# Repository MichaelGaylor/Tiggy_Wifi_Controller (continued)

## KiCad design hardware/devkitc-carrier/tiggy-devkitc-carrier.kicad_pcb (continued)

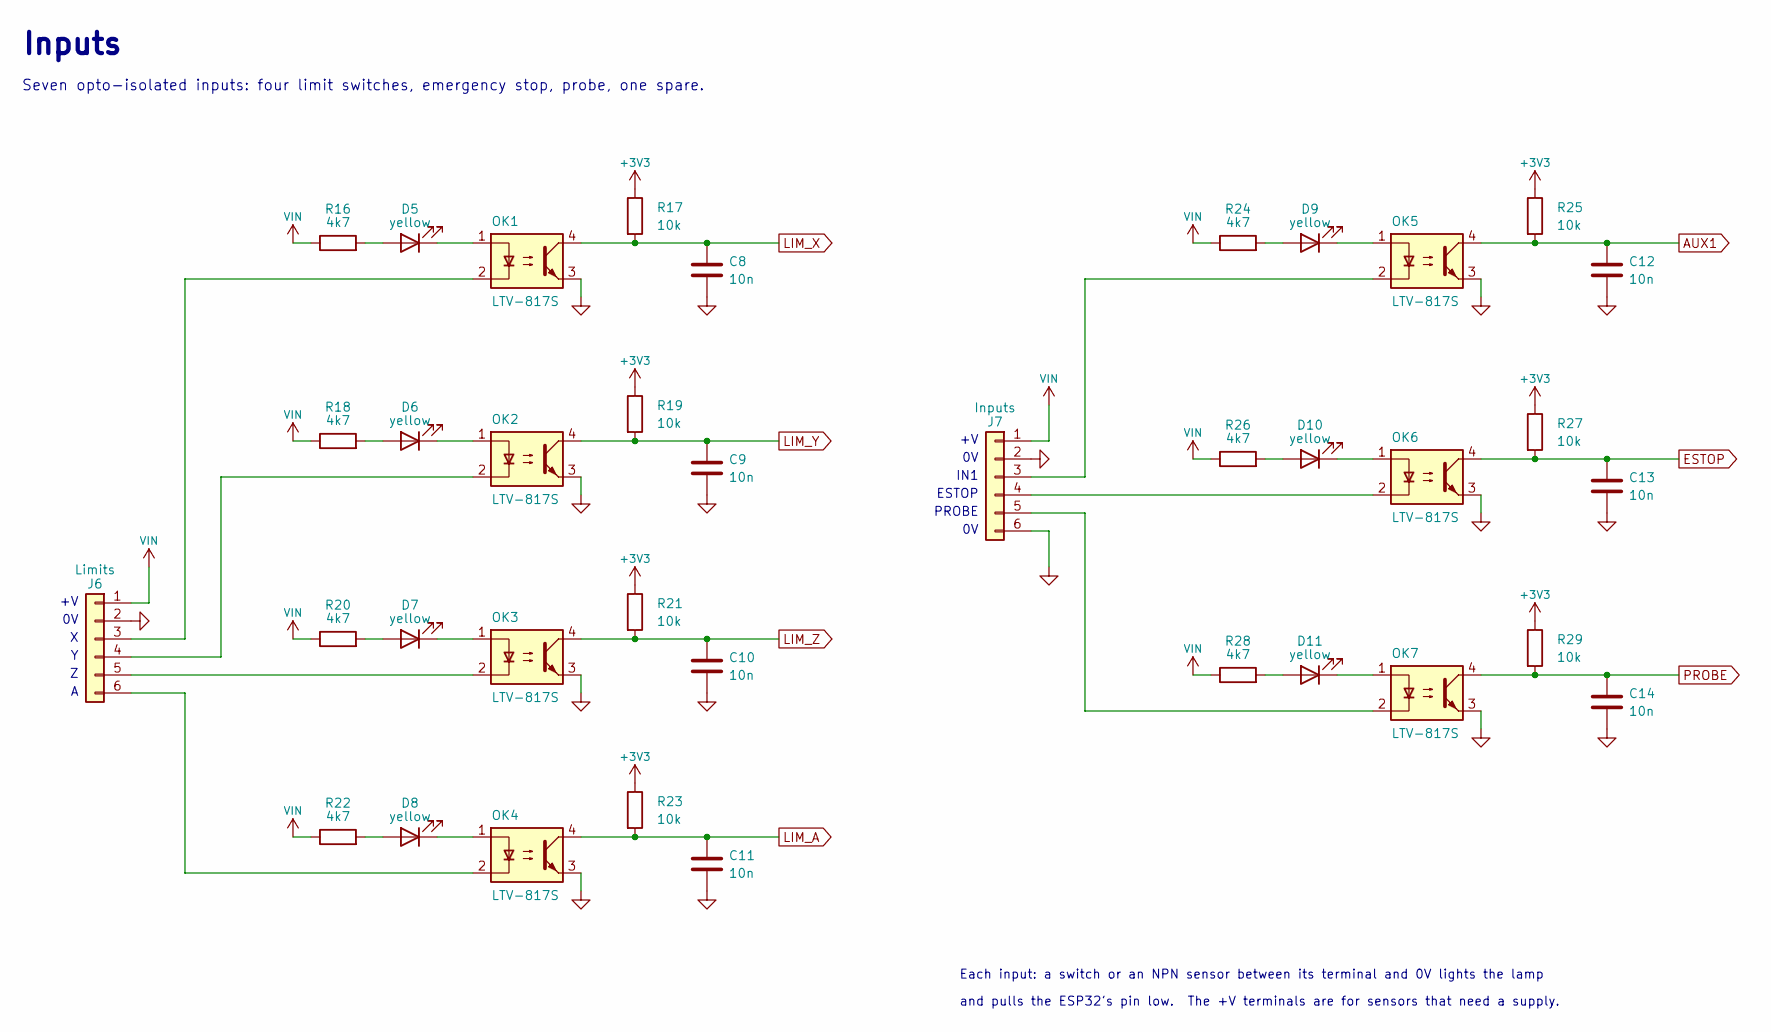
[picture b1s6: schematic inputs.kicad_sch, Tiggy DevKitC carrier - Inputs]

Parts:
C8, C9, C10, C11, C12, C13, C14: 10n; C_0603_1608Metric
D5, D6, D7, D8, D9, D10, D11: yellow; LED_0805_2012Metric
J6: Limits; PhoenixContact_MC_1,5_6-G-3.81_1x06_P3.81mm_Horizontal
J7: Inputs; PhoenixContact_MC_1,5_6-G-3.81_1x06_P3.81mm_Horizontal
OK1, OK2, OK3, OK4, OK5, OK6, OK7: LTV-817S; SMDIP-4_W9.53mm
R16, R18, R20, R22, R24, R26, R28: 4k7; R_1206_3216Metric
R17, R19, R21, R23, R25, R27, R29: 10k; R_0603_1608Metric

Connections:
+3V3: R17.1, R19.1, R21.1, R23.1, R25.1, R27.1, R29.1; also elsewhere on the board
AUX1: C12.1, OK5.4, R25.2; also elsewhere on the board
ESTOP: C13.1, OK6.4, R27.2; also elsewhere on the board
GND: C8.2, C9.2, C10.2, C11.2, C12.2, C13.2, C14.2, J6.2, J7.2, J7.6, OK1.3, OK2.3, OK3.3, OK4.3, OK5.3, OK6.3, OK7.3; also elsewhere on the board
LIM_A: C11.1, OK4.4, R23.2; also elsewhere on the board
LIM_X: C8.1, OK1.4, R17.2; also elsewhere on the board
LIM_Y: C9.1, OK2.4, R19.2; also elsewhere on the board
LIM_Z: C10.1, OK3.4, R21.2; also elsewhere on the board
unnamed: D5.2 (A), R16.2
unnamed: D5.1 (K), OK1.1
unnamed: D6.2 (A), R18.2
unnamed: D6.1 (K), OK2.1
unnamed: D7.2 (A), R20.2
unnamed: D7.1 (K), OK3.1
unnamed: D8.2 (A), R22.2
unnamed: D8.1 (K), OK4.1
unnamed: D9.2 (A), R24.2
unnamed: D9.1 (K), OK5.1
unnamed: D10.2 (A), R26.2
unnamed: D10.1 (K), OK6.1
unnamed: D11.2 (A), R28.2
unnamed: D11.1 (K), OK7.1
unnamed: J6.3, OK1.2
unnamed: J6.4, OK2.2
unnamed: J6.5, OK3.2
unnamed: J6.6, OK4.2
unnamed: J7.3, OK5.2
unnamed: J7.4, OK6.2
unnamed: J7.5, OK7.2
PROBE: C14.1, OK7.4, R29.2; also elsewhere on the board
VIN: J6.1, J7.1, R16.1, R18.1, R20.1, R22.1, R24.1, R26.1, R28.1; also elsewhere on the board

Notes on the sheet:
IN1
ESTOP
PROBE
Each input: a switch or an NPN sensor between its terminal and 0V lights the lamp
and pulls the ESP32's pin low. The +V terminals are for sensors that need a supply.
Inputs
Seven opto-isolated inputs: four limit switches, emergency stop, probe, one spare.

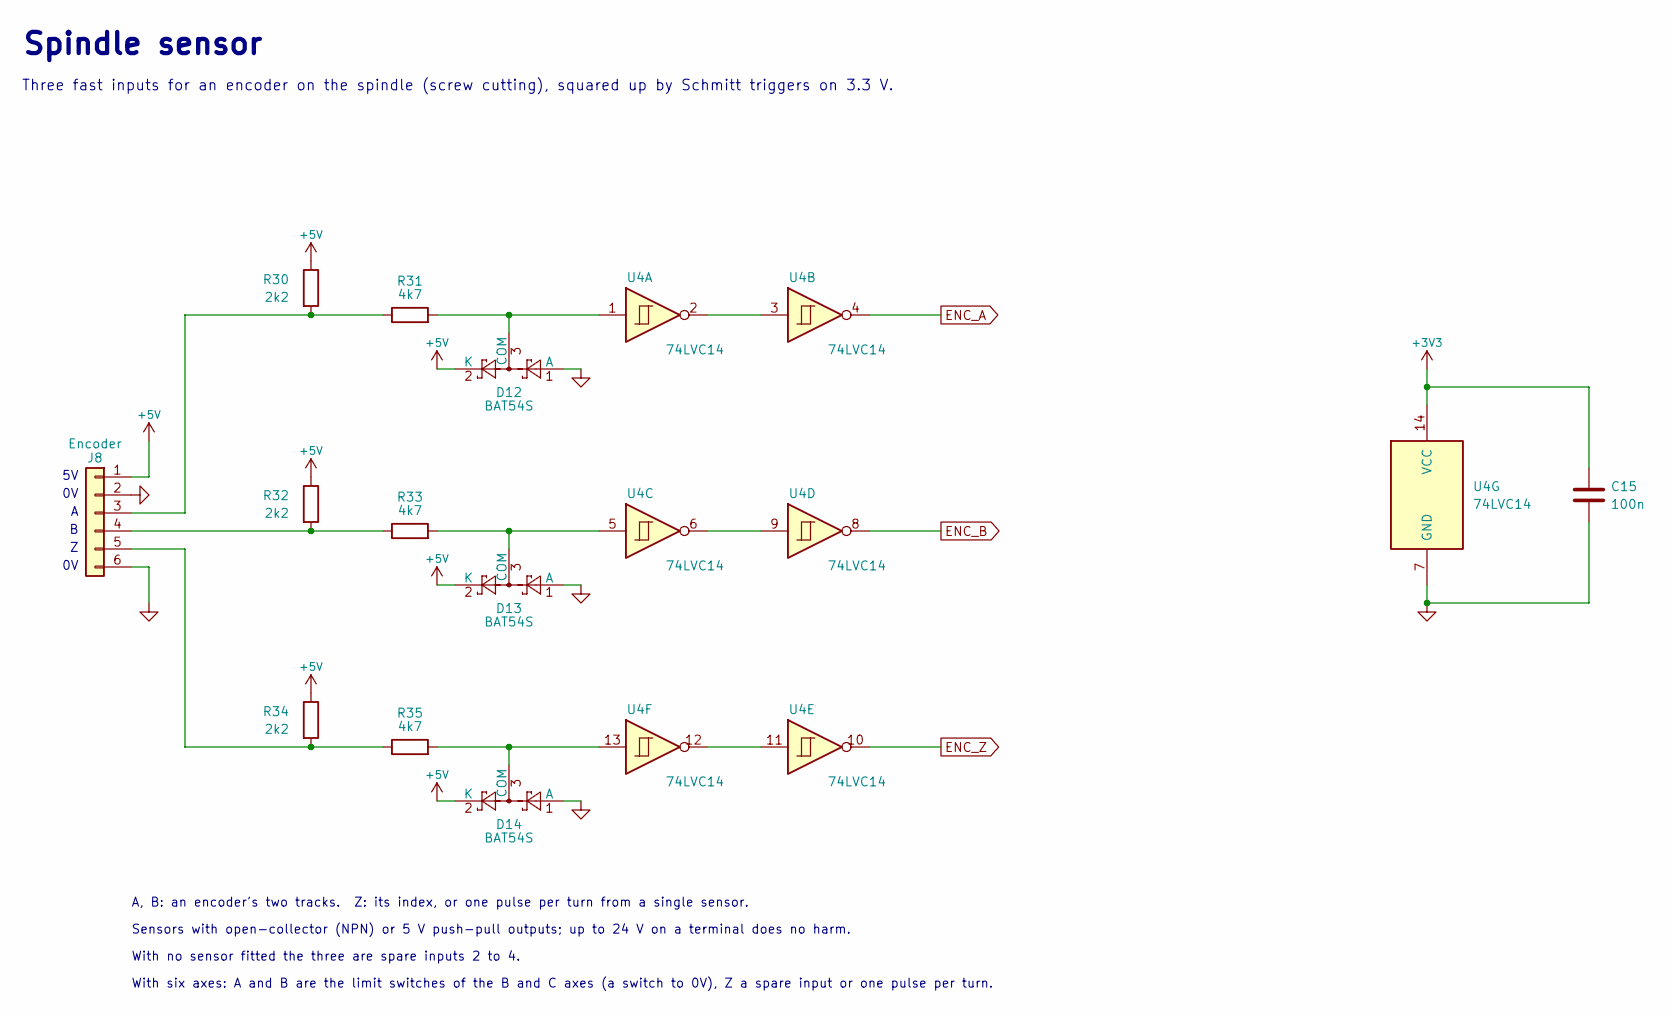
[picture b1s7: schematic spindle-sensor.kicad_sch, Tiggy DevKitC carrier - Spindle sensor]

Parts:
C15: 100n; C_0603_1608Metric
D12, D13, D14: BAT54S; SOT-23
J8: Encoder; PhoenixContact_MC_1,5_6-G-3.81_1x06_P3.81mm_Horizontal
R30, R32, R34: 2k2; R_0603_1608Metric
R31, R33, R35: 4k7; R_0805_2012Metric
U4: 74LVC14; SOIC-14_3.9x8.7mm_P1.27mm

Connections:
+3V3: C15.1, U4.14 (VCC); also elsewhere on the board
+5V: D12.2 (K), D13.2 (K), D14.2 (K), J8.1, R30.1, R32.1, R34.1; also elsewhere on the board
ENC_A: U4.4; also elsewhere on the board
ENC_B: U4.8; also elsewhere on the board
ENC_Z: U4.10; also elsewhere on the board
GND: C15.2, D12.1 (A), D13.1 (A), D14.1 (A), J8.2, J8.6, U4.7 (GND); also elsewhere on the board
unnamed: D12.3 (COM), R31.2, U4.1
unnamed: D13.3 (COM), R33.2, U4.5
unnamed: D14.3 (COM), R35.2, U4.13
unnamed: J8.3, R30.2, R31.1
unnamed: J8.4, R32.2, R33.1
unnamed: J8.5, R34.2, R35.1
unnamed: U4.2, U4.3
unnamed: U4.6, U4.9
unnamed: U4.11, U4.12

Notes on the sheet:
A, B: an encoder's two tracks. Z: its index, or one pulse per turn from a single sensor.
Sensors with open-collector (NPN) or 5 V push-pull outputs; up to 24 V on a terminal does no harm.
With no sensor fitted the three are spare inputs 2 to 4.
With six axes: A and B are the limit switches of the B and C axes (a switch to 0V), Z a spare input or one pulse per turn.
Spindle sensor
Three fast inputs for an encoder on the spindle (screw cutting), squared up by Schmitt triggers on 3.3 V.

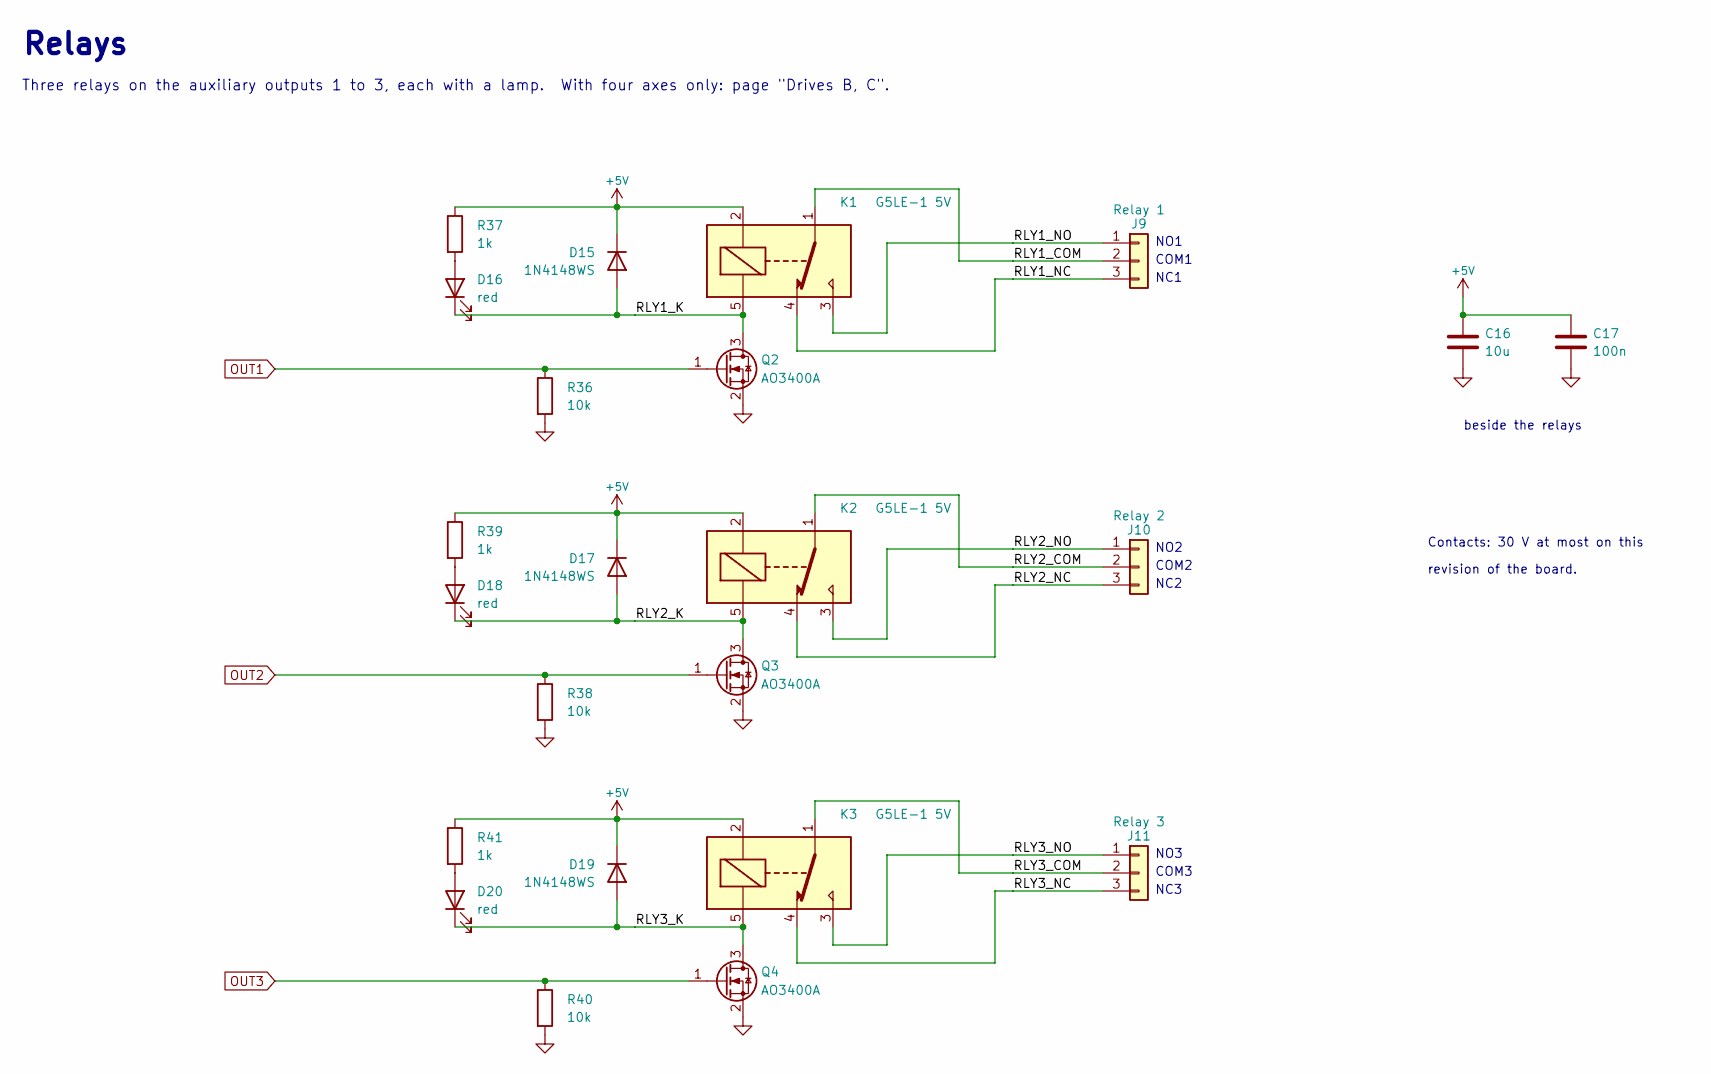
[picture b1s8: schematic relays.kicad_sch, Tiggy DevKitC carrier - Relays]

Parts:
C16: 10u; C_1206_3216Metric
C17: 100n; C_0603_1608Metric
D15, D17, D19: 1N4148WS; D_SOD-323
D16, D18, D20: red; LED_0805_2012Metric
J9: Relay 1; PhoenixContact_MSTBA_2,5_3-G-5,08_1x03_P5.08mm_Horizontal
J10: Relay 2; PhoenixContact_MSTBA_2,5_3-G-5,08_1x03_P5.08mm_Horizontal
J11: Relay 3; PhoenixContact_MSTBA_2,5_3-G-5,08_1x03_P5.08mm_Horizontal
K1, K2, K3: G5LE-1 5V; Relay_SPDT_Omron-G5LE-1
Q2, Q3, Q4: AO3400A; SOT-23
R36, R38, R40: 10k; R_0603_1608Metric
R37, R39, R41: 1k; R_0603_1608Metric

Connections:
+5V: C16.1, C17.1, D15.1 (K), D17.1 (K), D19.1 (K), K1.2, K2.2, K3.2, R37.1, R39.1, R41.1; also elsewhere on the board
/Relays/RLY1_COM: J9.2, K1.1
/Relays/RLY1_K: D15.2 (A), D16.1 (K), K1.5, Q2.3 (D)
/Relays/RLY1_NC: J9.3, K1.4
/Relays/RLY1_NO: J9.1, K1.3
/Relays/RLY2_COM: J10.2, K2.1
/Relays/RLY2_K: D17.2 (A), D18.1 (K), K2.5, Q3.3 (D)
/Relays/RLY2_NC: J10.3, K2.4
/Relays/RLY2_NO: J10.1, K2.3
/Relays/RLY3_COM: J11.2, K3.1
/Relays/RLY3_K: D19.2 (A), D20.1 (K), K3.5, Q4.3 (D)
/Relays/RLY3_NC: J11.3, K3.4
/Relays/RLY3_NO: J11.1, K3.3
GND: C16.2, C17.2, Q2.2 (S), Q3.2 (S), Q4.2 (S), R36.2, R38.2, R40.2; also elsewhere on the board
unnamed: D16.2 (A), R37.2
unnamed: D18.2 (A), R39.2
unnamed: D20.2 (A), R41.2
OUT1: Q2.1 (G), R36.1; also elsewhere on the board
OUT2: Q3.1 (G), R38.1; also elsewhere on the board
OUT3: Q4.1 (G), R40.1; also elsewhere on the board

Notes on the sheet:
NO1
COM1
NC1
NO2
COM2
NC2
NO3
COM3
NC3
beside the relays
Contacts: 30 V at most on this
revision of the board.
Relays
Three relays on the auxiliary outputs 1 to 3, each with a lamp. With four axes only: page "Drives B, C".

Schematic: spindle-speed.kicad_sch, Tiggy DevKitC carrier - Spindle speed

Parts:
C18: 100n; C_0603_1608Metric
C19: 4u7; C_0603_1608Metric
C20: 100n 50V; C_0603_1608Metric
J12: Spindle; PhoenixContact_MC_1,5_6-G-3.81_1x06_P3.81mm_Horizontal
R10, R42, R43, R44, R45: 10k; R_0603_1608Metric
R46: 100R; R_0603_1608Metric
U3: 74AHCT125; SOIC-14_3.9x8.7mm_P1.27mm
U5: LM358; SOIC-8_3.9x4.9mm_P1.27mm

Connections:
+5V: C18.1, J12.5, U3.1, U3.13, U3.14 (VCC); also elsewhere on the board
/Spindle speed/AO_T: J12.1, R46.2
/Spindle speed/CP_O: J12.4, U3.8
/Spindle speed/PWM_5V: J12.3, R43.1, U3.6
CPUMP: R42.1, U3.9; also elsewhere on the board
GND: C18.2, C19.2, C20.2, J12.2, J12.6, R10.2, R42.2, R45.2, U3.2, U3.4, U3.7 (GND), U3.10, U3.12, U5.4 (V-), U5.5 (+); also elsewhere on the board
unnamed: R44.1, R46.1, U5.1
unnamed: C19.1, R43.2, U5.3 (+)
unnamed: R44.2, R45.1, U5.2 (-)
unnamed: U5.6 (-), U5.7
SPINDLE: R10.1, U3.5; also elsewhere on the board
VIN: C20.1, U5.8 (V+); also elsewhere on the board

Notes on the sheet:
0-10V
PWM
10 k, 4u7: ripple under 1 %
at 1 kHz
gain 2: 0 to 10 V
spare half, parked
The 0-10V output needs 12 V or more at the supply terminal to reach 10 V.
The charge pump is there with four axes only (jumpers, page "Drives B, C").
two gates not used, switched off
Spindle speed
The spindle's speed as PWM and as 0 to 10 V for a frequency converter, and the charge pump signal.

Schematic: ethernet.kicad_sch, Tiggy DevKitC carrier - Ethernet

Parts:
A2: USR-ES1 (W5500); USR-ES1_Socket
C21: 1u; C_0603_1608Metric
C22: 100n; C_0603_1608Metric
D21: 1N4148WS; D_SOD-323
JP1: CS to 0V; SolderJumper-2_P1.3mm_Open_RoundedPad1.0x1.5mm
Q1: 2N7002; SOT-23
R47: 4k7; R_0603_1608Metric
R48, R49, R51: 10k; R_0603_1608Metric
R50: 47k; R_0603_1608Metric
R52: 1k; R_0603_1608Metric

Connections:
+3V3: A2.8 (3V3), A2.9 (3V3), C22.1, R47.1, R48.1, R51.1; also elsewhere on the board
/Ethernet/CS_GATE: C21.1, D21.2 (A), Q1.1 (G), R50.2
/Ethernet/ETH_CS: A2.5 (SCSn), JP1.1 (A), Q1.3 (D), R51.2
EN: D21.1 (K), R50.1, R52.1; also elsewhere on the board
ETH_INT: A2.6 (INTn), R48.2; also elsewhere on the board
ETH_MISO: A2.12 (MISO), R49.1; also elsewhere on the board
ETH_MOSI: A2.3 (MOSI); also elsewhere on the board
ETH_SCLK: A2.4 (SCLK), R47.2; also elsewhere on the board
GND: A2.1 (GND), A2.2 (GND), A2.7 (GND), C21.2, C22.2, JP1.2 (B), Q1.2 (S), R49.2; also elsewhere on the board
unnamed: A2.11 (RSTn), R52.2

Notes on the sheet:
The firmware has no pin for chip select: it expects the module always selected. Here Q1 selects it
20 to 80 ms after the ESP32 leaves reset (47 k and 1 u), so that the module's data output cannot hold
GPIO46 high while the ESP32 reads it as a start-up option. D lets the capacitor empty at once on a reset.
JP1, bridged with solder, selects the module all the time (for a module that then stays off the bus).
Ethernet
Socket for a USR-ES1 (W5500) module.

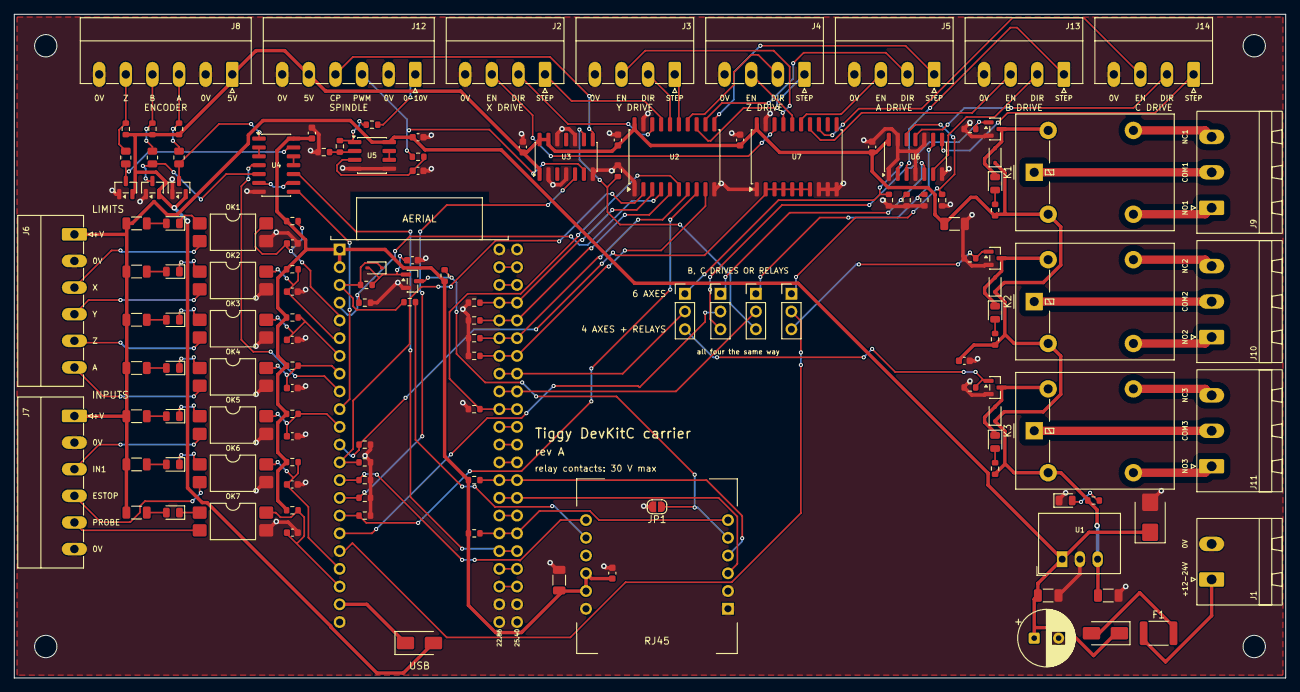
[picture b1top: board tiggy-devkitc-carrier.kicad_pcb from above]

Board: 2 copper layers, 182.0 x 95.0 mm, 142 parts (0 on the bottom side), 118 nets.

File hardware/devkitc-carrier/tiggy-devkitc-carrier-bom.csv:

"References","Value","Footprint","Quantity"
"A1","ESP32-S3-DevKitC-1","tiggy:ESP32-S3-DevKitC-1_Socket","1"
"A2","USR-ES1 (W5500)","tiggy:USR-ES1_Socket","1"
"C1","100u 35V","Capacitor_THT:CP_Radial_D8.0mm_P3.50mm","1"
"C2","10u 50V","Capacitor_SMD:C_1206_3216Metric","1"
"C3","22u 10V","Capacitor_SMD:C_1206_3216Metric","1"
"C4,C16","10u","Capacitor_SMD:C_1206_3216Metric","2"
"C5-C7,C15,C17,C18,C22","100n","Capacitor_SMD:C_0603_1608Metric","7"
"C8-C14","10n","Capacitor_SMD:C_0603_1608Metric","7"
"C19","4u7","Capacitor_SMD:C_0603_1608Metric","1"
"C20","100n 50V","Capacitor_SMD:C_0603_1608Metric","1"
"C21","1u","Capacitor_SMD:C_0603_1608Metric","1"
"D1,D3","SS34","Diode_SMD:D_SMA","2"
"D2","SMBJ28CA","Diode_SMD:D_SMB","1"
"D4","green","LED_SMD:LED_0805_2012Metric","1"
"D5-D11","yellow","LED_SMD:LED_0805_2012Metric","7"
"D12-D14","BAT54S","Package_TO_SOT_SMD:SOT-23","3"
"D15,D17,D19,D21","1N4148WS","Diode_SMD:D_SOD-323","4"
"D16,D18,D20","red","LED_SMD:LED_0805_2012Metric","3"
"F1","1.1A 33V","Fuse:Fuse_1812_4532Metric","1"
"J1","12-24V","Connector_Phoenix_MSTB:PhoenixContact_MSTBA_2,5_2-G-5,08_1x02_P5.08mm_Horizontal","1"
"J2","X drive","Connector_Phoenix_MC:PhoenixContact_MC_1,5_4-G-3.81_1x04_P3.81mm_Horizontal","1"
"J3","Y drive","Connector_Phoenix_MC:PhoenixContact_MC_1,5_4-G-3.81_1x04_P3.81mm_Horizontal","1"
"J4","Z drive","Connector_Phoenix_MC:PhoenixContact_MC_1,5_4-G-3.81_1x04_P3.81mm_Horizontal","1"
"J5","A drive","Connector_Phoenix_MC:PhoenixContact_MC_1,5_4-G-3.81_1x04_P3.81mm_Horizontal","1"
"J6","Limits","Connector_Phoenix_MC:PhoenixContact_MC_1,5_6-G-3.81_1x06_P3.81mm_Horizontal","1"
"J7","Inputs","Connector_Phoenix_MC:PhoenixContact_MC_1,5_6-G-3.81_1x06_P3.81mm_Horizontal","1"
"J8","Encoder","Connector_Phoenix_MC:PhoenixContact_MC_1,5_6-G-3.81_1x06_P3.81mm_Horizontal","1"
"J9","Relay 1","Connector_Phoenix_MSTB:PhoenixContact_MSTBA_2,5_3-G-5,08_1x03_P5.08mm_Horizontal","1"
"J10","Relay 2","Connector_Phoenix_MSTB:PhoenixContact_MSTBA_2,5_3-G-5,08_1x03_P5.08mm_Horizontal","1"
"J11","Relay 3","Connector_Phoenix_MSTB:PhoenixContact_MSTBA_2,5_3-G-5,08_1x03_P5.08mm_Horizontal","1"
"J12","Spindle","Connector_Phoenix_MC:PhoenixContact_MC_1,5_6-G-3.81_1x06_P3.81mm_Horizontal","1"
"J13","B drive","Connector_Phoenix_MC:PhoenixContact_MC_1,5_4-G-3.81_1x04_P3.81mm_Horizontal","1"
"J14","C drive","Connector_Phoenix_MC:PhoenixContact_MC_1,5_4-G-3.81_1x04_P3.81mm_Horizontal","1"
"JP2-JP5","3-pin header, jumper","Connector_PinHeader_2.54mm:PinHeader_1x03_P2.54mm_Vertical","4"
"K1-K3","G5LE-1 5V","Relay_THT:Relay_SPDT_Omron-G5LE-1","3"
"OK1-OK7","LTV-817S","Package_DIP:SMDIP-4_W9.53mm","7"
"Q1","2N7002","Package_TO_SOT_SMD:SOT-23","1"
"Q2-Q4","AO3400A","Package_TO_SOT_SMD:SOT-23","3"
"R1,R37,R39,R41,R52","1k","Resistor_SMD:R_0603_1608Metric","5"
"R2-R15,R17,R19,R21,R23,R25,R27,R29,R36,R38,R40,R42-R45,R48,R49,R51","10k","Resistor_SMD:R_0603_1608Metric","31"
"R16,R18,R20,R22,R24,R26,R28","4k7","Resistor_SMD:R_1206_3216Metric","7"
"R30,R32,R34","2k2","Resistor_SMD:R_0603_1608Metric","3"
"R31,R33,R35","4k7","Resistor_SMD:R_0805_2012Metric","3"
"R46","100R","Resistor_SMD:R_0603_1608Metric","1"
"R47","4k7","Resistor_SMD:R_0603_1608Metric","1"
"R50","47k","Resistor_SMD:R_0603_1608Metric","1"
"U1","R-78E5.0-1.0","Converter_DCDC:Converter_DCDC_RECOM_R-78E-0.5_THT","1"
"U2,U7","74AHCT541","Package_SO:SOIC-20W_7.5x12.8mm_P1.27mm","2"
"U3,U6","74AHCT125","Package_SO:SOIC-14_3.9x8.7mm_P1.27mm","2"
"U4","74LVC14","Package_SO:SOIC-14_3.9x8.7mm_P1.27mm","1"
"U5","LM358","Package_SO:SOIC-8_3.9x4.9mm_P1.27mm","1"

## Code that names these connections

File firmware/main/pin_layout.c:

/*
 * WiFi CNC Controller - What the terminals are used for
 *
 * See pin_layout.h.
 */

#include "pin_layout.h"
#include "pin_config.h"
#include "persist/nvs_config.h"
#include "../../protocol/wifi_cnc_protocol.h"

#include <stdbool.h>

/* Functions a board may not have at all */
#ifndef PIN_CHARGE_PUMP
#define PIN_CHARGE_PUMP GPIO_NUM_NC
#endif
#ifndef PIN_MISC_OUT_0
#define PIN_MISC_OUT_0  GPIO_NUM_NC
#endif
#ifndef PIN_MISC_OUT_1
#define PIN_MISC_OUT_1  GPIO_NUM_NC
#endif
#ifndef PIN_MISC_IN_0
#define PIN_MISC_IN_0   GPIO_NUM_NC
#endif
#ifndef PIN_MISC_IN_1
#define PIN_MISC_IN_1   GPIO_NUM_NC
#endif
#ifndef PIN_MISC_IN_2
#define PIN_MISC_IN_2   GPIO_NUM_NC
#endif
#ifndef PIN_MISC_IN_3
#define PIN_MISC_IN_3   GPIO_NUM_NC
#endif
#if !HAS_ETHERNET
#define PIN_ETH_MOSI    GPIO_NUM_NC
#define PIN_ETH_MISO    GPIO_NUM_NC
#define PIN_ETH_SCLK    GPIO_NUM_NC
#define PIN_ETH_INT     GPIO_NUM_NC
#endif

static int s_layout = -1, s_sensor = -1;

void pin_layout_reload(void)
{
    s_layout = nvs_config_get_u8("layout", PIN_LAYOUT_SIX_AXES) == PIN_LAYOUT_FOUR_AXES ? PIN_LAYOUT_FOUR_AXES
                                                                                        : PIN_LAYOUT_SIX_AXES;
    uint8_t mode = nvs_config_get_u8("enc_mode", 0);
    if (nvs_config_get_u16("enc_ppr", 0) == 0) s_sensor = PIN_SENSOR_NONE;
    else if (mode == 1) s_sensor = PIN_SENSOR_PULSE;
    else if (mode == 2) s_sensor = PIN_SENSOR_ENCODER;
    else s_sensor = PIN_SENSOR_ENCODER_INDEX;
}

int pin_layout(void)
{
    if (s_layout < 0) pin_layout_reload();
    return s_layout;
}

int pin_layout_sensor(void)
{
    if (s_sensor < 0) pin_layout_reload();
    return s_sensor;
}

/* As pin_config.h has it: six axes */
static gpio_num_t board_default(uint16_t key)
{
    switch (key) {
    case WCNC_CFG_PIN_STEP_X:        return PIN_STEP_X;
    case WCNC_CFG_PIN_STEP_Y:        return PIN_STEP_Y;
    case WCNC_CFG_PIN_STEP_Z:        return PIN_STEP_Z;
    case WCNC_CFG_PIN_STEP_A:        return PIN_STEP_A;
    case WCNC_CFG_PIN_STEP_B:        return PIN_STEP_B;
    case WCNC_CFG_PIN_STEP_C:        return PIN_STEP_C;
    case WCNC_CFG_PIN_DIR_X:         return PIN_DIR_X;
    case WCNC_CFG_PIN_DIR_Y:         return PIN_DIR_Y;
    case WCNC_CFG_PIN_DIR_Z:         return PIN_DIR_Z;
    case WCNC_CFG_PIN_DIR_A:         return PIN_DIR_A;
    case WCNC_CFG_PIN_DIR_B:         return PIN_DIR_B;
    case WCNC_CFG_PIN_DIR_C:         return PIN_DIR_C;
    case WCNC_CFG_PIN_ENABLE:        return PIN_ENABLE;
    case WCNC_CFG_PIN_LIMIT_X:       return PIN_LIMIT_X;
    case WCNC_CFG_PIN_LIMIT_Y:       return PIN_LIMIT_Y;
    case WCNC_CFG_PIN_LIMIT_Z:       return PIN_LIMIT_Z;
    case WCNC_CFG_PIN_LIMIT_A:       return PIN_LIMIT_A;
    case WCNC_CFG_PIN_LIMIT_B:       return PIN_LIMIT_B;
    case WCNC_CFG_PIN_LIMIT_C:       return PIN_LIMIT_C;
    case WCNC_CFG_PIN_PROBE:         return PIN_PROBE;
    case WCNC_CFG_PIN_ESTOP:         return PIN_ESTOP;
    case WCNC_CFG_PIN_SPINDLE:       return PIN_SPINDLE_EN;
    case WCNC_CFG_PIN_LED:           return PIN_STATUS_LED;
    case WCNC_CFG_PIN_CHARGE_PUMP:   return PIN_CHARGE_PUMP;
    case WCNC_CFG_PIN_MISC_OUT0:     return PIN_MISC_OUT_0;
    case WCNC_CFG_PIN_MISC_OUT1:     return PIN_MISC_OUT_1;
    case WCNC_CFG_PIN_ENCODER_A:     return PIN_ENCODER_A;
    case WCNC_CFG_PIN_ENCODER_B:     return PIN_ENCODER_B;
    case WCNC_CFG_PIN_ENCODER_INDEX: return PIN_ENCODER_INDEX;
    case WCNC_CFG_PIN_MISC_IN0:      return PIN_MISC_IN_0;
    case WCNC_CFG_PIN_MISC_IN1:      return PIN_MISC_IN_1;
    case WCNC_CFG_PIN_MISC_IN2:      return PIN_MISC_IN_2;
    case WCNC_CFG_PIN_MISC_IN3:      return PIN_MISC_IN_3;
    case WCNC_CFG_PIN_ETH_MOSI:      return PIN_ETH_MOSI;
    case WCNC_CFG_PIN_ETH_MISO:      return PIN_ETH_MISO;
    case WCNC_CFG_PIN_ETH_SCLK:      return PIN_ETH_SCLK;
    case WCNC_CFG_PIN_ETH_INT:       return PIN_ETH_INT;
    default:                         return GPIO_NUM_NC;
    }
}

#if defined(BOARD_ESP32S3_DEVKITC) || defined(BOARD_ESP32S3_ZERO)
/* A terminal the spindle sensor shares with another job: the sensor's while
 * a sensor of a kind that needs it is set up, the other job's otherwise.
 * 'sensor_key' is the sensor input the terminal can be (encoder A, B or the
 * index), 'key' the function being asked about. */
static bool shared(uint16_t key, uint16_t sensor_key, uint16_t other_key, gpio_num_t terminal, gpio_num_t *pin)
{
    if (key != sensor_key && key != other_key) return false;
    int sensor = pin_layout_sensor();
    bool taken = sensor_key == WCNC_CFG_PIN_ENCODER_INDEX
                     ? (sensor == PIN_SENSOR_ENCODER_INDEX || sensor == PIN_SENSOR_PULSE)
                     : (sensor == PIN_SENSOR_ENCODER_INDEX || sensor == PIN_SENSOR_ENCODER);
    *pin = (key == sensor_key) == taken ? terminal : GPIO_NUM_NC;
    return true;
}
#endif

/* What differs from pin_config.h.  False: nothing does for this function. */
static bool layout_default(uint16_t key, gpio_num_t *pin)
{
    bool four = pin_layout() == PIN_LAYOUT_FOUR_AXES;
    (void)four;

#if defined(BOARD_ESP32S3_DEVKITC)
    if (four) {
        switch (key) {
        case WCNC_CFG_PIN_STEP_B:  case WCNC_CFG_PIN_DIR_B:  case WCNC_CFG_PIN_LIMIT_B:
        case WCNC_CFG_PIN_STEP_C:  case WCNC_CFG_PIN_DIR_C:  case WCNC_CFG_PIN_LIMIT_C:
            *pin = GPIO_NUM_NC;
            return true;
        default:
            break;
        }
    }
#endif

#if defined(BOARD_ESP32S3_DEVKITC_OCTAL)
    /* The index pulse, or a single sensor, goes on what is otherwise
     * auxiliary input 2: an input either way.  A single sensor can go there
     * even with six axes; an encoder's index only when the encoder itself
     * has terminals, which takes four. */
    if (key == WCNC_CFG_PIN_ENCODER_INDEX || key == WCNC_CFG_PIN_MISC_IN1) {
        int sensor = pin_layout_sensor();
        bool index = sensor == PIN_SENSOR_PULSE || (four && sensor == PIN_SENSOR_ENCODER_INDEX);
        *pin = (key == WCNC_CFG_PIN_ENCODER_INDEX) == index ? GPIO_NUM_21 : GPIO_NUM_NC;
        return true;
    }
    if (four) {
        if (shared(key, WCNC_CFG_PIN_ENCODER_A, WCNC_CFG_PIN_MISC_IN2, GPIO_NUM_16, pin)) return true;
        if (shared(key, WCNC_CFG_PIN_ENCODER_B, WCNC_CFG_PIN_MISC_IN3, GPIO_NUM_17, pin)) return true;
        switch (key) {
        case WCNC_CFG_PIN_MISC_OUT0:    *pin = GPIO_NUM_11; return true;
        case WCNC_CFG_PIN_MISC_OUT1:    *pin = GPIO_NUM_12; return true;
        case WCNC_CFG_PIN_MISC_OUT2:    *pin = GPIO_NUM_40; return true;
        case WCNC_CFG_PIN_CHARGE_PUMP:  *pin = GPIO_NUM_39; return true;
        default:                        return false;
        }
    }
    return false;

#elif defined(BOARD_ESP32S3_DEVKITC_QUAD)
    /* GPIO 37 is spare whatever the layout: a single sensor can go there
     * even with six axes (an encoder's index only when the encoder itself
     * has terminals, which takes four) */
    if (key == WCNC_CFG_PIN_ENCODER_INDEX) {
        int sensor = pin_layout_sensor();
        *pin = (sensor == PIN_SENSOR_PULSE || (four && sensor == PIN_SENSOR_ENCODER_INDEX)) ? GPIO_NUM_37 : GPIO_NUM_NC;
        return true;
    }
    if (four) {
        if (shared(key, WCNC_CFG_PIN_ENCODER_A, WCNC_CFG_PIN_MISC_IN3, GPIO_NUM_16, pin)) return true;
        if (key == WCNC_CFG_PIN_ENCODER_B) {
            int sensor = pin_layout_sensor();
            *pin = (sensor == PIN_SENSOR_ENCODER_INDEX || sensor == PIN_SENSOR_ENCODER) ? GPIO_NUM_17 : GPIO_NUM_NC;
            return true;
        }
        switch (key) {
        case WCNC_CFG_PIN_MISC_OUT2:    *pin = GPIO_NUM_40; return true;
        case WCNC_CFG_PIN_MISC_OUT3:    *pin = GPIO_NUM_39; return true;
        case WCNC_CFG_PIN_MISC_OUT4:    *pin = GPIO_NUM_34; return true;
        default:                        return false;
        }
    }
    return false;

#elif defined(BOARD_ESP32S3_ZERO)
    /* The sensor terminals are there in either layout; free ones are inputs */
    if (shared(key, WCNC_CFG_PIN_ENCODER_A, WCNC_CFG_PIN_MISC_IN0, GPIO_NUM_15, pin)) return true;
    if (shared(key, WCNC_CFG_PIN_ENCODER_B, WCNC_CFG_PIN_MISC_IN1, GPIO_NUM_16, pin)) return true;
    if (shared(key, WCNC_CFG_PIN_ENCODER_INDEX, WCNC_CFG_PIN_MISC_IN2, GPIO_NUM_17, pin)) return true;
    return false;

#else
    (void)key;
    (void)pin;
    return false;
#endif
}

gpio_num_t pin_layout_default(uint16_t key)
{
    gpio_num_t pin;
    if (layout_default(key, &pin)) return pin;
    return board_default(key);
}

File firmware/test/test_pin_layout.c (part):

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 *
 * A wrong pin number cannot be found by any simulator: it shows when someone
 * wires a machine.  This goes through every layout and every kind of
 * spindle sensor of one board and checks what can be checked without it:
 *   - no terminal is given two jobs;
 *   - no job is put on a pin the board cannot spare (flash and PSRAM, USB,
 *     the serial console) or cannot drive (input-only pins);
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    { WCNC_CFG_PIN_STEP_A, "A step", true },   { WCNC_CFG_PIN_DIR_A, "A dir", true },   { WCNC_CFG_PIN_LIMIT_A, "A limit", false },
    { WCNC_CFG_PIN_STEP_B, "B step", true },   { WCNC_CFG_PIN_DIR_B, "B dir", true },   { WCNC_CFG_PIN_LIMIT_B, "B limit", false },
    { WCNC_CFG_PIN_STEP_C, "C step", true },   { WCNC_CFG_PIN_DIR_C, "C dir", true },   { WCNC_CFG_PIN_LIMIT_C, "C limit", false },
    { WCNC_CFG_PIN_ENABLE, "enable", true },   { WCNC_CFG_PIN_PROBE, "probe", false },  { WCNC_CFG_PIN_ESTOP, "E-stop", false },
    { WCNC_CFG_PIN_SPINDLE, "spindle", true }, { WCNC_CFG_PIN_LED, "LED", true },       { WCNC_CFG_PIN_CHARGE_PUMP, "charge pump", true },
    { WCNC_CFG_PIN_MISC_OUT0, "aux out 1", true }, { WCNC_CFG_PIN_MISC_OUT1, "aux out 2", true },
    { WCNC_CFG_PIN_MISC_OUT2, "aux out 3", true }, { WCNC_CFG_PIN_MISC_OUT3, "aux out 4", true },
    { WCNC_CFG_PIN_MISC_OUT4, "aux out 5", true },
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                                             WCNC_CFG_PIN_MISC_IN0, WCNC_CFG_PIN_MISC_IN1, WCNC_CFG_PIN_MISC_IN2, WCNC_CFG_PIN_MISC_IN3,
                                             WCNC_CFG_PIN_CHARGE_PUMP, WCNC_CFG_PIN_MISC_OUT0, WCNC_CFG_PIN_MISC_OUT1,
                                             WCNC_CFG_PIN_MISC_OUT2, WCNC_CFG_PIN_MISC_OUT3, WCNC_CFG_PIN_MISC_OUT4 };
            static const char *LABEL[] = { "A", "B", "index", "in1", "in2", "in3", "in4", "pump", "out1", "out2", "out3", "out4", "out5" };
            for (int i = 0; i < (int)(sizeof(SHOW) / sizeof(SHOW[0])); i++) {
                int pin = pin_of(SHOW[i]);
                if (pin >= 0) printf(" %s=%d", LABEL[i], pin);
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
